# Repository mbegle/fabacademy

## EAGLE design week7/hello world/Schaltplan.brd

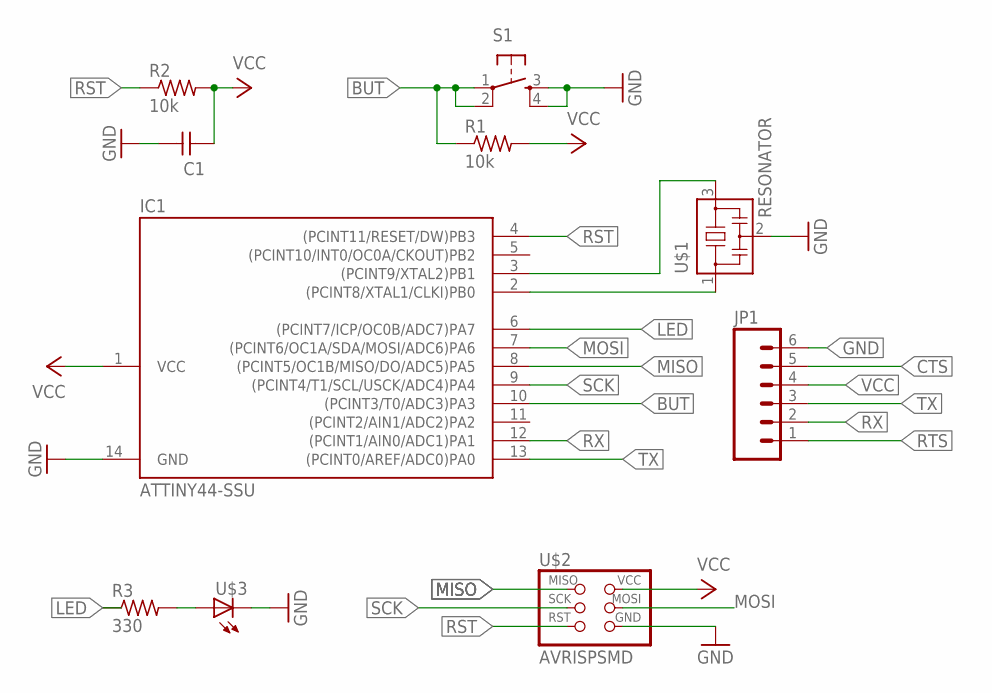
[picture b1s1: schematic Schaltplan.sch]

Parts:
C1: UNPOLARIZED_CAPACITOR1206; 1206
IC1: ATTINY44-SSU; SOIC14
JP1: M06SMD; 1X06-SMD
R1, R2: 10k; 1206
R3: 330; 1206
S1: 6MM_SWITCH6MM_SWITCH; 6MM_SWITCH
U$1: RESONATOR; EFOBM
U$2: AVRISPSMD; 2X03SMD
U$3: LED1206; 1206

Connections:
BUT: IC1.10 ((PCINT3/T0/ADC3)PA3), R1.1, S1.1, S1.2 (P1)
CTS: JP1.5
GND: C1.2, IC1.14 (GND), JP1.6, S1.3 (S), S1.4 (S1), U$1.2, U$2.6 (GND), U$3.2 (C)
LED: IC1.6 ((PCINT7/ICP/OC0B/ADC7)PA7), R3.1
MISO: IC1.8 ((PCINT5/OC1B/MISO/DO/ADC5)PA5), U$2.1 (MISO)
MOSI: IC1.7 ((PCINT6/OC1A/SDA/MOSI/ADC6)PA6), U$2.4 (MOSI)
unnamed: IC1.2 ((PCINT8/XTAL1/CLKI)PB0), U$1.1
unnamed: IC1.3 ((PCINT9/XTAL2)PB1), U$1.3
unnamed: R3.2, U$3.1 (A)
RST: IC1.4 ((PCINT11/RESET/DW)PB3), R2.1, U$2.5 (RST)
RTS: JP1.1
RX: IC1.12 ((PCINT1/AIN0/ADC1)PA1), JP1.2
SCK: IC1.9 ((PCINT4/T1/SCL/USCK/ADC4)PA4), U$2.3 (SCK)
TX: IC1.13 ((PCINT0/AREF/ADC0)PA0), JP1.3
VCC: C1.1, IC1.1 (VCC), JP1.4, R1.2, R2.2, U$2.2 (VCC)

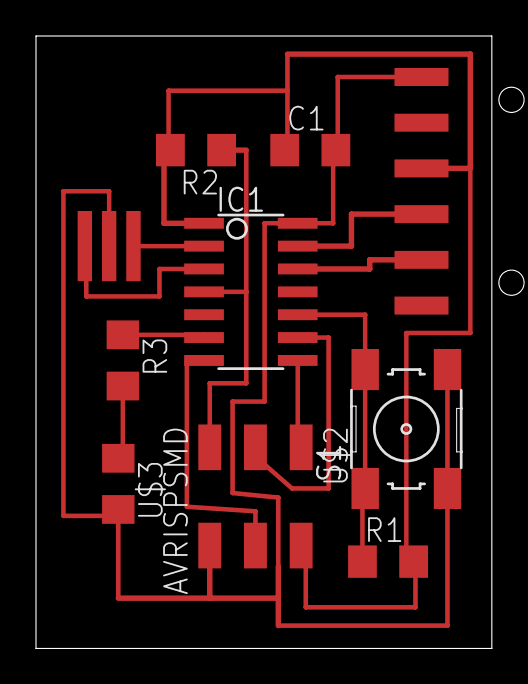
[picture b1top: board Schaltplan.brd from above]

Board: 2 copper layers, 25.3 x 34.0 mm, 10 parts (0 on the bottom side), 13 nets.

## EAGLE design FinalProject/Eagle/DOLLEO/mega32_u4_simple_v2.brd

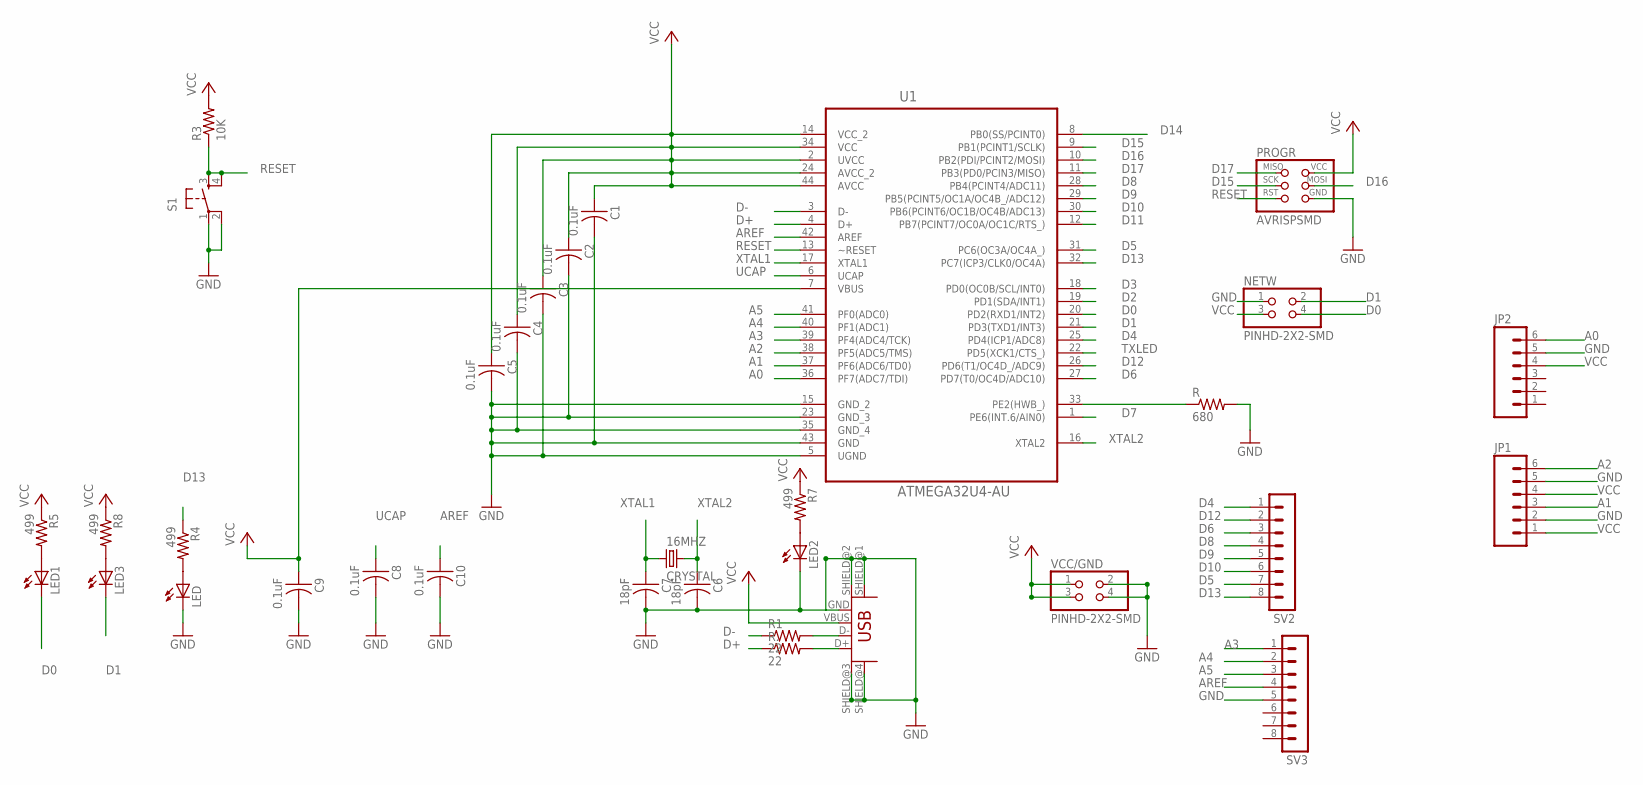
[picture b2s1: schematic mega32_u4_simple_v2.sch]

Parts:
16MHZ: CRYSTAL; 2-SMD-5X3MM
C1, C2, C3, C4, C5, C8, C9, C10: 0.1uF; C1206FAB
C6, C7: 18pF; C1206FAB
JP1, JP2: M06SMD; 1X06-SMD
LED, LED1, LED2, LED3: LED1206; 1206
NETW: PINHD-2X2-SMD; 2X02SMD
PROGR: AVRISPSMD; 2X03SMD
R: 680; R1206FAB
R1, R.: 22; R1206FAB
R3: 10K; R1206FAB
R4, R5, R7, R8: 499; 1206
S1: 6MM_SWITCH6MM_SWITCH; 6MM_SWITCH
SV2, SV3: MA08-1
U1: ATMEGA32U4-AU; QFP80P1200X1200X120-44N
U$1: USB_MINIB
VCC/GND: PINHD-2X2-SMD; 2X02SMD

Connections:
A0: JP2.6, U1.36 (PF7(ADC7/TDI))
A1: JP1.3, U1.37 (PF6(ADC6/TD0))
A2: JP1.6, U1.38 (PF5(ADC5/TMS))
A3: SV3.1, U1.39 (PF4(ADC4/TCK))
A4: SV3.2, U1.40 (PF1(ADC1))
A5: SV3.3, U1.41 (PF0(ADC0))
AREF: C10.1, SV3.4, U1.42 (AREF)
D0: LED1.2 (C), NETW.4, U1.20 (PD2(RXD1/INT2))
D1: LED3.2 (C), NETW.2, U1.21 (PD3(TXD1/INT3))
D2: U1.19 (PD1(SDA/INT1))
D3: U1.18 (PD0(OC0B/SCL/INT0))
D4: SV2.1, U1.25 (PD4(ICP1/ADC8))
D5: SV2.7, U1.31 (PC6(OC3A/OC4A_))
D6: SV2.3, U1.27 (PD7(T0/OC4D/ADC10))
D7: U1.1 (PE6(INT.6/AIN0))
D8: SV2.4, U1.28 (PB4(PCINT4/ADC11))
D9: SV2.5, U1.29 (PB5(PCINT5/OC1A/OC4B_/ADC12))
D10: SV2.6, U1.30 (PB6(PCINT6/OC1B/OC4B/ADC13))
D11: U1.12 (PB7(PCINT7/OC0A/OC1C/RTS_))
D12: SV2.2, U1.26 (PD6(T1/OC4D_/ADC9))
D13: R4.1, SV2.8, U1.32 (PC7(ICP3/CLK0/OC4A))
D14: U1.8 (PB0(SS/PCINT0))
D15: PROGR.3 (SCK), U1.9 (PB1(PCINT1/SCLK))
D16: PROGR.4 (MOSI), U1.10 (PB2(PDI/PCINT2/MOSI))
D17: PROGR.1 (MISO), U1.11 (PB3(PD0/PCIN3/MISO))
D+: R..1, U1.4 (D+)
D-: R1.1, U1.3 (D-)
GND: C1.2, C2.2, C3.2, C4.2, C5.2, C6.2, C7.2, C8.2, C9.2, C10.2, JP1.2, JP1.5, JP2.5, LED.2 (C), LED2.2 (C), NETW.1, PROGR.6 (GND), R.2, S1.1, S1.2 (P1), SV3.5, U1.5 (UGND), U1.15 (GND_2), U1.23 (GND_3), U1.35 (GND_4), U1.43 (GND), U$1.GND, U$1.SHIELD@1 (SHIELD), U$1.SHIELD@2 (SHIELD1), U$1.SHIELD@3 (SHIELD2), U$1.SHIELD@4 (SHIELD3), VCC/GND.2, VCC/GND.4
unnamed: R1.2, U$1.D-
unnamed: R..2, U$1.D+
unnamed: LED.1 (A), R4.2
unnamed: LED1.1 (A), R5.2
unnamed: LED2.1 (A), R7.2
unnamed: LED3.1 (A), R8.2
unnamed: R.1, U1.33 (PE2(HWB_))
RESET: PROGR.5 (RST), R3.1, S1.3 (S), S1.4 (S1), U1.13 (~RESET)
TXLED: U1.22 (PD5(XCK1/CTS_))
UCAP: C8.1, U1.6 (UCAP)
VCC: C1.1, C2.1, C3.1, C4.1, C5.1, C9.1, JP1.1, JP1.4, JP2.4, NETW.3, PROGR.2 (VCC), R3.2, R5.1, R7.1, R8.1, U1.2 (UVCC), U1.7 (VBUS), U1.14 (VCC_2), U1.24 (AVCC_2), U1.34 (VCC), U1.44 (AVCC), U$1.VBUS, VCC/GND.1, VCC/GND.3
XTAL1: 16MHZ.P$1 (1), C7.1, U1.17 (XTAL1)
XTAL2: 16MHZ.P$2 (2), C6.1, U1.16 (XTAL2)

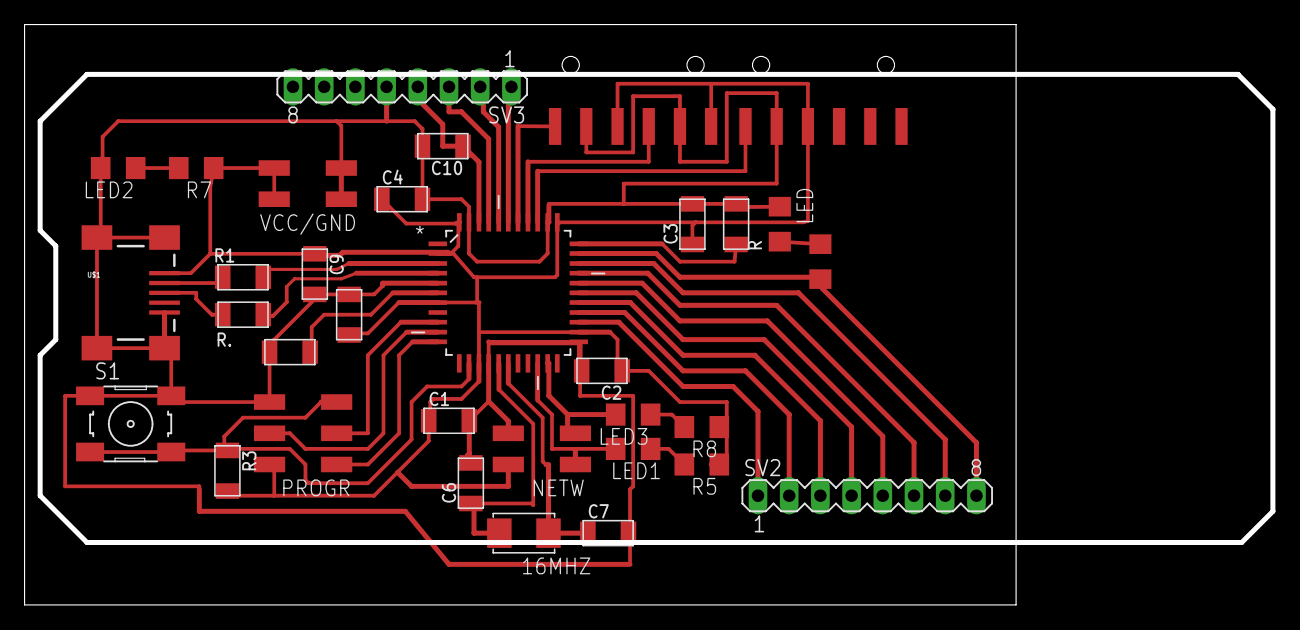
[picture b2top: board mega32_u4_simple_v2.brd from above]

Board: 2 copper layers, 101.6 x 47.2 mm, 33 parts (0 on the bottom side), 35 nets.

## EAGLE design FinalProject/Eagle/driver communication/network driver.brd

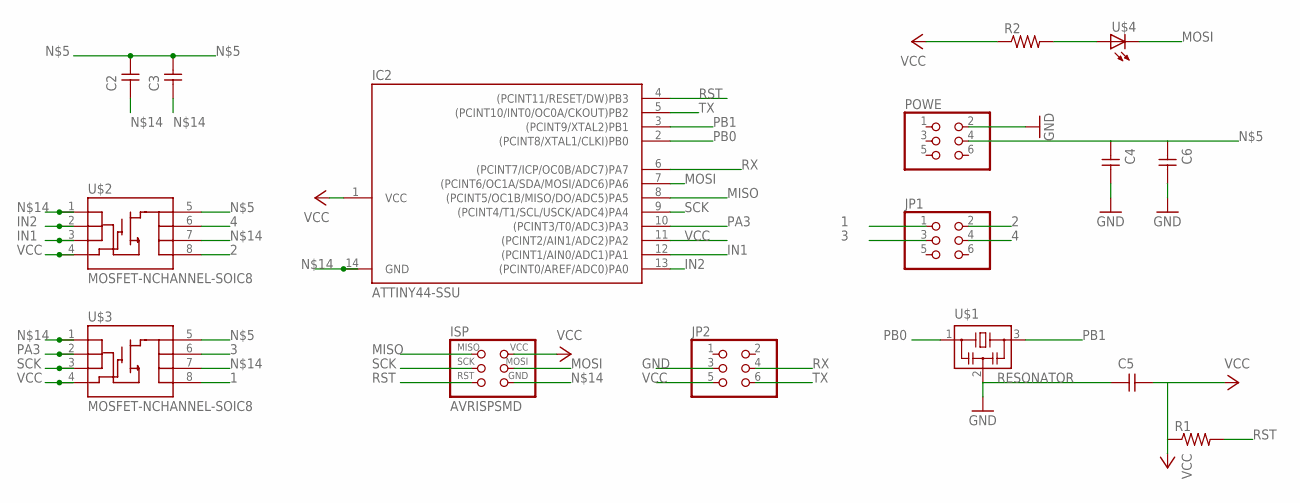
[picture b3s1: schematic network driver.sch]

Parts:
C2, C3, C4, C5, C6: UNPOLARIZED_CAPACITOR1206; 1206
IC2: ATTINY44-SSU; SOIC14
ISP: AVRISPSMD; 2X03SMD
JP1, JP2: PINHD-2X3-SMD; 2X03SMD
POWE: PINHD-2X3-SMD; 2X03SMD
R1, R2: RESISTOR1206; 1206
U$1: RESONATOR; EFOBM
U$2, U$3: MOSFET-NCHANNEL-SOIC8; SO08
U$4: LED1206; 1206

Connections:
1: JP1.1, U$3.8 (D)
2: JP1.2, U$2.8 (D)
3: JP1.3, U$3.6 (D)
4: JP1.4, U$2.6 (D)
GND: C5.1, JP2.3, U$1.2
IN1: IC2.12 ((PCINT1/AIN0/ADC1)PA1), U$2.3 (S)
IN2: IC2.13 ((PCINT0/AREF/ADC0)PA0), U$2.2 (S)
MISO: IC2.8 ((PCINT5/OC1B/MISO/DO/ADC5)PA5), ISP.1 (MISO)
MOSI: IC2.7 ((PCINT6/OC1A/SDA/MOSI/ADC6)PA6), ISP.4 (MOSI), U$4.2 (C)
unnamed: R2.2, U$4.1 (A)
unnamed: C2.2, C3.2, C4.1, C6.1, POWE.4, U$2.5 (D), U$3.5 (D)
unnamed: C2.1, C3.1, C4.2, C6.2, IC2.14 (GND), ISP.6 (GND), POWE.2, U$2.1 (S), U$2.7 (D), U$3.1 (S), U$3.7 (D)
PA3: IC2.10 ((PCINT3/T0/ADC3)PA3), U$3.2 (S)
PB0: IC2.2 ((PCINT8/XTAL1/CLKI)PB0), U$1.1
PB1: IC2.3 ((PCINT9/XTAL2)PB1), U$1.3
RST: IC2.4 ((PCINT11/RESET/DW)PB3), ISP.5 (RST), R1.2
RX: IC2.6 ((PCINT7/ICP/OC0B/ADC7)PA7), JP2.4
SCK: IC2.9 ((PCINT4/T1/SCL/USCK/ADC4)PA4), ISP.3 (SCK), U$3.3 (S)
TX: IC2.5 ((PCINT10/INT0/OC0A/CKOUT)PB2), JP2.6
VCC: C5.2, IC2.1 (VCC), IC2.11 ((PCINT2/AIN1/ADC2)PA2), ISP.2 (VCC), JP2.5, R1.1, R2.1, U$2.4 (G), U$3.4 (G)

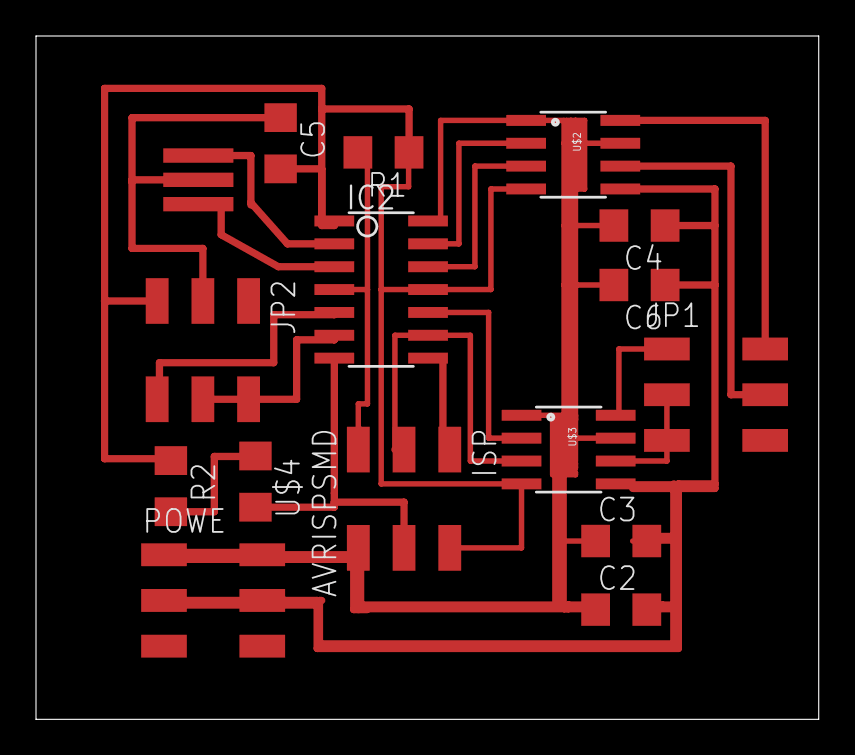
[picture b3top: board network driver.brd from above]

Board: 2 copper layers, 43.5 x 38.0 mm, 16 parts (0 on the bottom side), 20 nets.

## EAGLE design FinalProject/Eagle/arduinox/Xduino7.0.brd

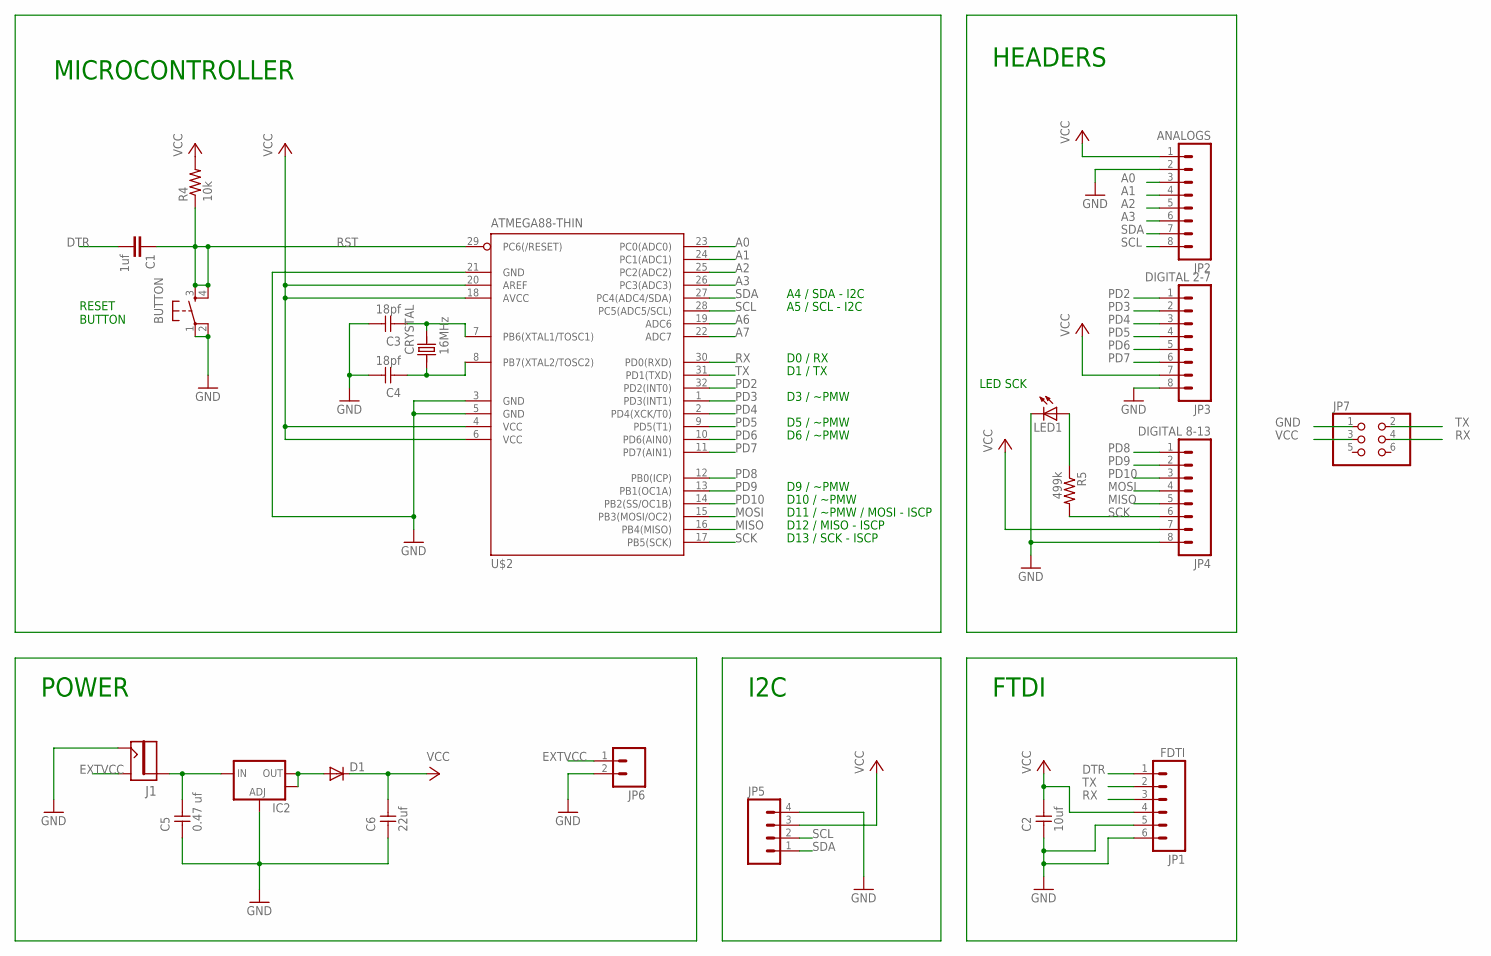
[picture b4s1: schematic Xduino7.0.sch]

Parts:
BUTTON: 6MM_SWITCH6MM_SWITCH; 6MM_SWITCH
C1: 1uf; 1206
C2: 10uf; 1206
C3, C4: 18pf; 1206
C5: 0.47 uf; 1206
C6: 22uf; 1206
CRYSTAL: 16MHz; CS10
D1: DIODESOD123; SOD123
IC2: V_REG_LM1117SOT223; SOT223
J1: JACK.65MM; JACK_.65MM
JP1: FDTI; 1X06-SMD_EDGE
JP2: ANALOGS; 1X08
JP3: DIGITAL 2-7; 1X08
JP4: DIGITAL 8-13; 1X08
JP5: M04PTH; 1X04
JP6: M02PTH; 1X02
JP7: PINHD-2X3-SMD; 2X03SMD
LED1: LED1206; 1206
R4: 10k; 1206
R5: 499k; 1206
U$2: ATMEGA88-THIN; TQFP32-08THIN

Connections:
A0: JP2.3, U$2.23 (PC0(ADC0))
A1: JP2.4, U$2.24 (PC1(ADC1))
A2: JP2.5, U$2.25 (PC2(ADC2))
A3: JP2.6, U$2.26 (PC3(ADC3))
A6: U$2.19 (ADC6)
A7: U$2.22 (ADC7)
DTR: C1.2, JP1.1
EXTVCC: J1.CONTACT (SHUNT), JP6.1
GND: BUTTON.1, BUTTON.2 (P1), C2.1, C3.2, C4.2, C5.1, C6.1, IC2.1 (ADJ), J1.SHUNT (CONTACT), JP1.5, JP1.6, JP2.2, JP3.8, JP4.8, JP5.4, JP6.2, JP7.1, LED1.2 (C), U$2.3 (GND), U$2.5 (GND), U$2.21 (GND)
MISO: JP4.5, U$2.16 (PB4(MISO))
MOSI: JP4.4, U$2.15 (PB3(MOSI/OC2))
unnamed: LED1.1 (A), R5.1
unnamed: C5.2, IC2.3 (IN), J1.PIN
unnamed: C4.1, CRYSTAL.P$1 (1), U$2.8 (PB7(XTAL2/TOSC2))
unnamed: C3.1, CRYSTAL.P$2 (2), U$2.7 (PB6(XTAL1/TOSC1))
unnamed: D1.ANODE (A), IC2.2 (OUT), IC2.4 (OUT)
PD2: JP3.1, U$2.32 (PD2(INT0))
PD3: JP3.2, U$2.1 (PD3(INT1))
PD4: JP3.3, U$2.2 (PD4(XCK/T0))
PD5: JP3.4, U$2.9 (PD5(T1))
PD6: JP3.5, U$2.10 (PD6(AIN0))
PD7: JP3.6, U$2.11 (PD7(AIN1))
PD8: JP4.1, U$2.12 (PB0(ICP))
PD9: JP4.2, U$2.13 (PB1(OC1A))
PD10: JP4.3, U$2.14 (PB2(SS/OC1B))
RST: BUTTON.3 (S), BUTTON.4 (S1), C1.1, R4.1, U$2.29 (PC6(/RESET))
RX: JP1.3, JP7.4, U$2.30 (PD0(RXD))
SCK: JP4.6, R5.2, U$2.17 (PB5(SCK))
SCL: JP2.8, JP5.2, U$2.28 (PC5(ADC5/SCL))
SDA: JP2.7, JP5.1, U$2.27 (PC4(ADC4/SDA))
TX: JP1.2, JP7.2, U$2.31 (PD1(TXD))
VCC: C2.2, C6.2, D1.CATHODE (C), JP1.4, JP2.1, JP3.7, JP4.7, JP5.3, JP7.3, R4.2, U$2.4 (VCC), U$2.6 (VCC), U$2.18 (AVCC), U$2.20 (AREF)

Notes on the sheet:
D5 / ~PMW
D6 / ~PMW
D9 / ~PMW
D10 / ~PMW
D11 / ~PMW / MOSI - ISCP
D12 / MISO - ISCP
D13 / SCK - ISCP
D0 / RX
A4 / SDA - I2C
A5 / SCL - I2C
D1 / TX
D3 / ~PMW
RESET BUTTON
MICROCONTROLLER
FTDI
HEADERS
LED SCK
POWER
I2C

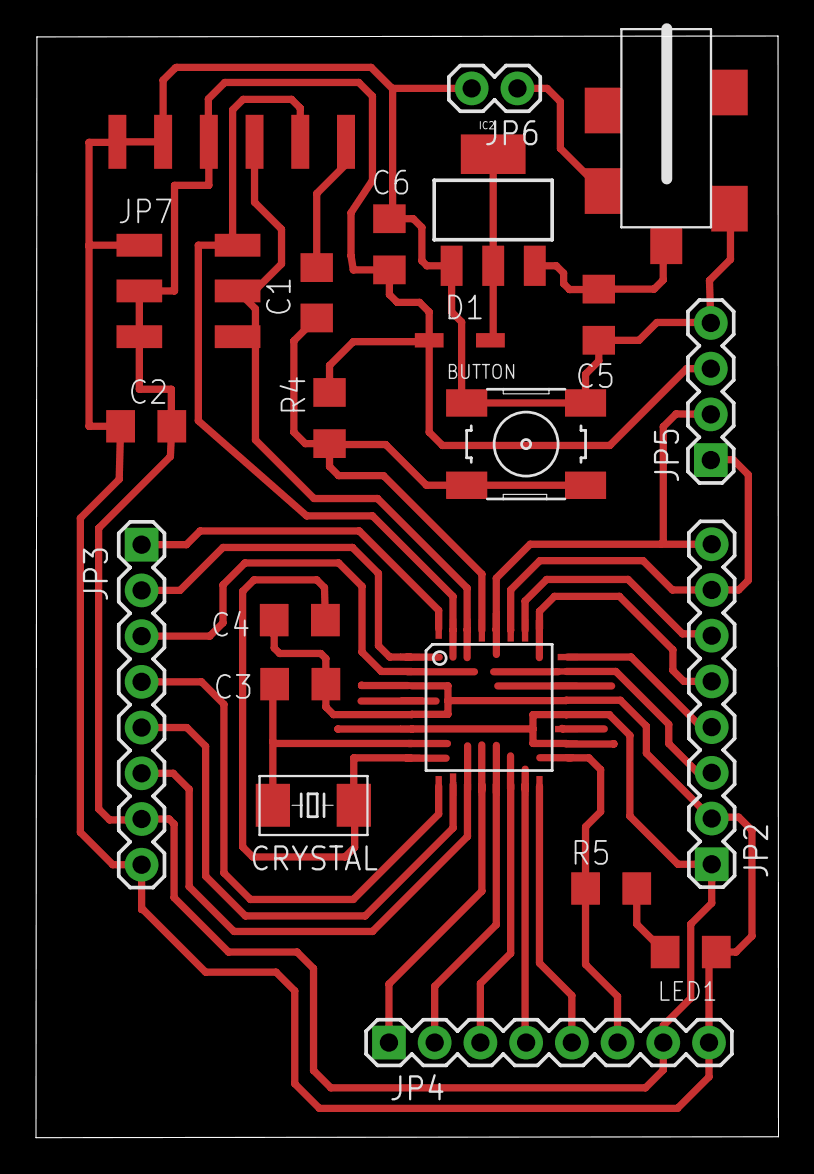
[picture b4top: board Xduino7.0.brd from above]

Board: 2 copper layers, 41.2 x 61.2 mm, 22 parts (0 on the bottom side), 30 nets.

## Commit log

2014-06-04 Hello Board
2014-06-04 w8w10
2014-06-06 composite

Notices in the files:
parts and their libraries:
01_SparkFun: Licensing: CC v3.0 Share-Alike You are welcome to use this library for commercial purposes.
